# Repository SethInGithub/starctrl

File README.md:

# StarCTRL
 A macropad that contains 11 MX switches, 1 rotary encoder, and 1 OLED screen to provide its user with the most options possible

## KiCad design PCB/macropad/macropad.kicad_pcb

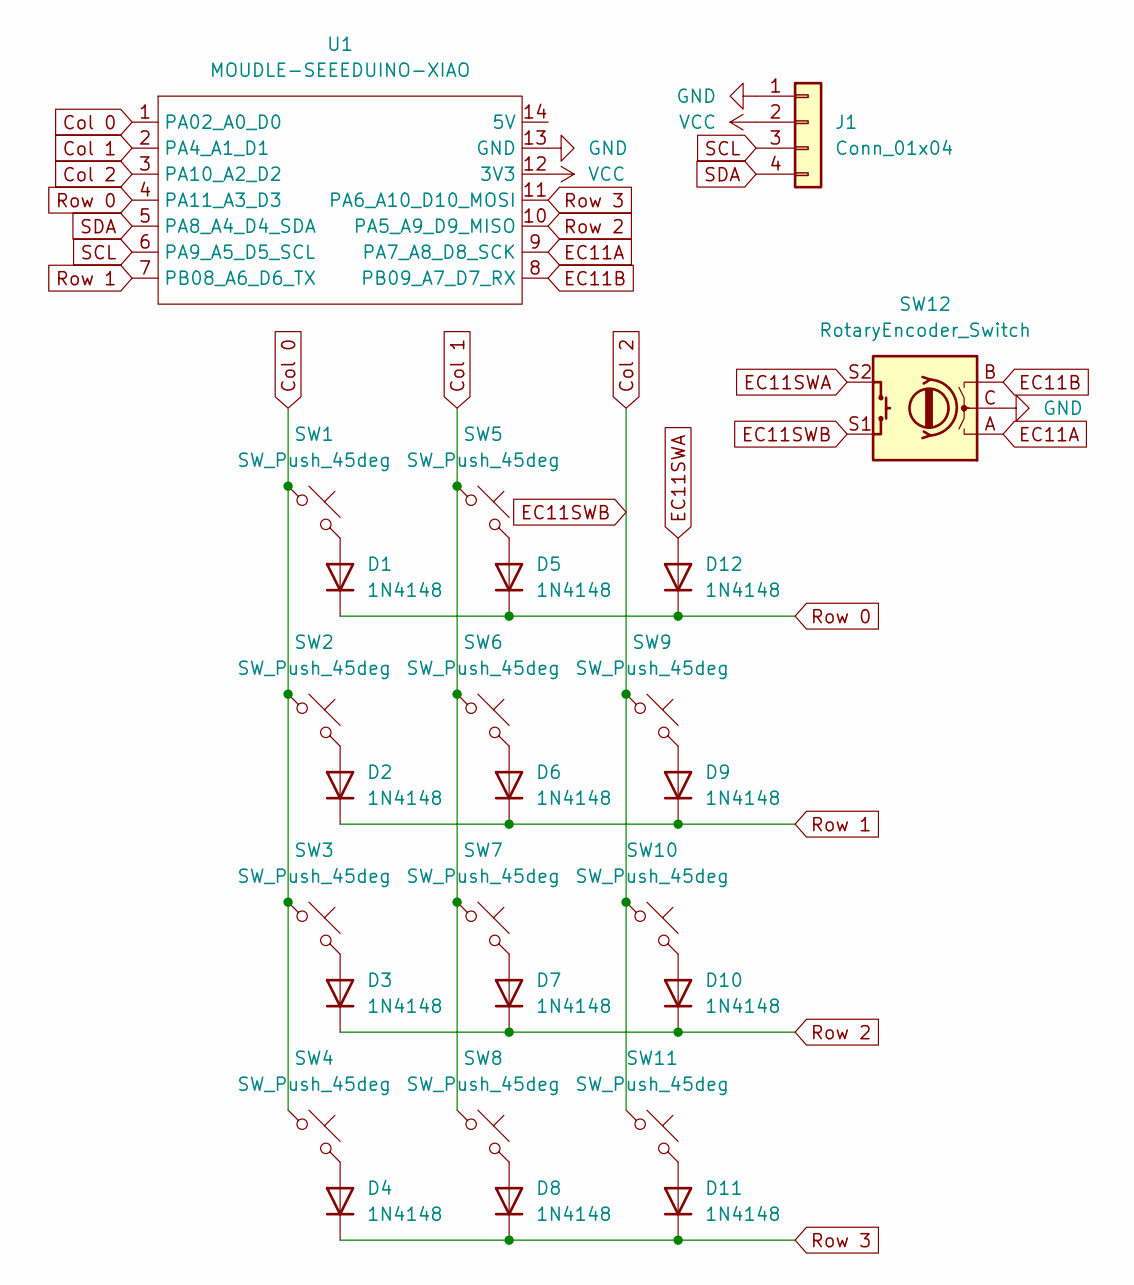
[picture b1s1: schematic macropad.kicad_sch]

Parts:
D1, D2, D3, D4, D5, D6, D7, D8, D9, D10, D11, D12: 1N4148; D_DO-35_SOD27_P7.62mm_Horizontal
J1: Conn_01x04; SSD1306-0.91-OLED-4pin-128x32
SW1, SW2, SW3, SW4, SW5, SW6, SW7, SW8, SW9, SW10, SW11: SW_Push_45deg; SW_Cherry_MX_1.00u_PCB
SW12: RotaryEncoder_Switch; RotaryEncoder_Alps_EC11E-Switch_Vertical_H20mm
U1: MOUDLE-SEEEDUINO-XIAO; XIAO-Generic-Hybrid-14P-2.54-21X17.8MM

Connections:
Col 0: SW1.1, SW2.1, SW3.1, SW4.1, U1.1 (PA02_A0_D0)
Col 1: SW5.1, SW6.1, SW7.1, SW8.1, U1.2 (PA4_A1_D1)
Col 2: SW9.1, SW10.1, SW11.1, SW12.S1, U1.3 (PA10_A2_D2)
EC11A: SW12.A, U1.9 (PA7_A8_D8_SCK)
EC11B: SW12.B, U1.8 (PB09_A7_D7_RX)
EC11SWA: D12.2 (A), SW12.S2
GND: J1.1, SW12.C, U1.13 (GND)
unnamed: D1.2 (A), SW1.2
unnamed: D2.2 (A), SW2.2
unnamed: D3.2 (A), SW3.2
unnamed: D4.2 (A), SW4.2
unnamed: D5.2 (A), SW5.2
unnamed: D6.2 (A), SW6.2
unnamed: D7.2 (A), SW7.2
unnamed: D8.2 (A), SW8.2
unnamed: D9.2 (A), SW9.2
unnamed: D10.2 (A), SW10.2
unnamed: D11.2 (A), SW11.2
Row 0: D1.1 (K), D5.1 (K), D12.1 (K), U1.4 (PA11_A3_D3)
Row 1: D2.1 (K), D6.1 (K), D9.1 (K), U1.7 (PB08_A6_D6_TX)
Row 2: D3.1 (K), D7.1 (K), D10.1 (K), U1.10 (PA5_A9_D9_MISO)
Row 3: D4.1 (K), D8.1 (K), D11.1 (K), U1.11 (PA6_A10_D10_MOSI)
SCL: J1.3, U1.6 (PA9_A5_D5_SCL)
SDA: J1.4, U1.5 (PA8_A4_D4_SDA)
VCC: J1.2, U1.12 (3V3)

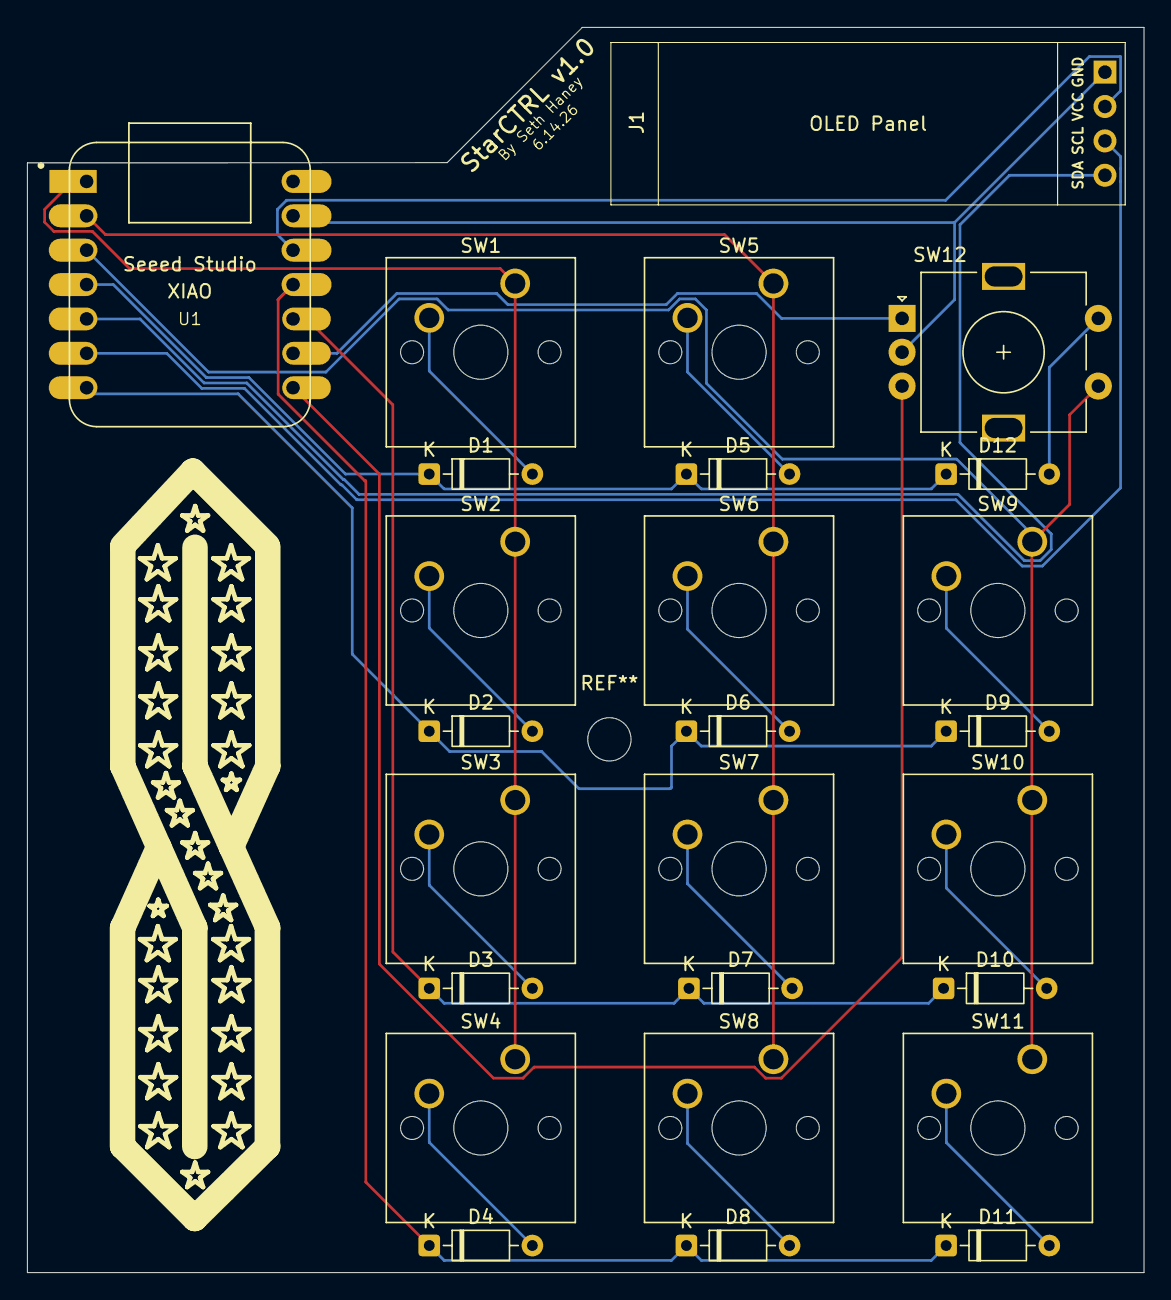
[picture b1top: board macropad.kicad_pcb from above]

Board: 2 copper layers, 82.5 x 92.0 mm, 26 parts (0 on the bottom side), 25 nets.

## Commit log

2026-06-15 Created Initial KiCad Files
2026-06-15 Created Basic Schematic and PCB
2026-06-15 Wired components together on PCB
2026-06-15 Update README with correct title and description
    Corrected capitalization and added a brief description of the macropad.
2026-06-15 Rename project from Macropad to StarCTRL
2026-06-15 Update macropad PCB: silk, footprint, gerbers
    Add fabrication-toolkit-options.json and Production/gerbers.zip. Modify macropad.kicad_pcb to change drillshape to 0 and set CAM outputdirectory to ../../Production/, add a MountingHole_3.2mm_M3 foot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
2026-06-15 Add assembled/production STEP files and PCB locks
    Add exported CAD and board STEP models plus KiCad lock files. Files included: CAD/assembled-model.step (full assembly export), Production/Top.step and Production/Bottom.step (manufacturing views), bo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
